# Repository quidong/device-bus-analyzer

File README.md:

# device-bus-analyzer

Collect, store, decode and inspect the internal bus telegrams of household appliances without ever transmitting on the bus.
Protocols: **BSH D-Bus** (Bosch / Siemens / Neff dishwashers) and the **Electrolux/AEG MACS bus** (heat-pump dryers; findings with confirmed/assumed/unknown status, see `docs/protocols/macs.md`; run detection names the run by the programme chosen before the start).

```
ESP32 board on the appliance bus ──ESPHome native API──▶ collector ─▶ SQLite (raw bursts, append-only)
                                                                         │
                                          decoder library + protocol spec (confirmed / assumed / unknown)
                                                                         │
                                    read-only HTTP API ─▶ web frontend (login) ─▶ MCP server (Claude Desktop)
```

* **Passive by design.** The collector only connects and subscribes to the device log; there is no code path that
  sends anything to a device or to the bus. The HTTP API is GET-only (a test asserts this). The web UI manages the local
  device list (add, edit, pause, delete with all its data) and never writes to an appliance.
* **Raw first.** Every burst is stored unchanged; decoded frames can be rebuilt at any time (`dba rebuild`), so better
  decoders never require re-recording.
* **Findings are data.** `src/device_bus_analyzer/spec/<protocol>.yaml` drives both the decoder and the findings page. Each
  command and field carries a status (`confirmed`, `assumed`, `unknown`) and its evidence.
* **No private data in the repository.** Logs stay on your server. `dba sanitize` strips SSID, MAC, IP, hostnames and keys
  before you share a log; a test scans the repository for such leftovers.

Hardware: the MACS board (schematic, KiCad, Gerber, enclosure) is in [`hardware/`](hardware/README.md).

## Quick start (Portainer / Docker)

1. Flash an ESPHome board with firmware that emits Logformat 1 (`docs/LOGFORMAT.md`). The matching ESPHome YAML for each device is shown in the app under **Devices > Firmware** (copy or download); the files live in `src/device_bus_analyzer/firmware/`: `bshdbus-analysis.example.yaml` for the dishwasher, `macs-analysis.example.yaml` + `macs_recorder.h` for the dryer.
   Enable the API encryption key in ESPHome.
2. In Portainer create a stack (Web editor: paste `docker-compose.yml`; the image `ghcr.io/quidong/device-bus-analyzer:latest` is built by GitHub Actions on every push to `main`) and set these **stack variables** (nothing secret is stored in the repo). Devices are *not* stack variables any more, add them in the UI (step 3):

| Variable | Meaning |
|---|---|
| `DBA_DEVICES` | *optional, one-time import*: `name@host[:port]/protocol`, comma separated, for example `geschirrspueler@192.0.2.10:6053/bshdbus` |
| `DBA_KEY_<NAME>` | *optional, one-time import*: ESPHome API encryption key of that device (`DBA_KEY_GESCHIRRSPUELER`) |
| `ADMIN_EMAIL` | the single admin account (login = e-mail address) |
| `ADMIN_PASSWORD_HASH` | argon2id hash, create with `echo -n 'your password' \| docker run -i --rm ghcr.io/quidong/device-bus-analyzer:latest dba hash-password` |
| `ADMIN_PASSWORD` | alternative to the hash (plain text in the stack; the hash is preferred) |
| `SESSION_SECRET` | optional: created on the first start and kept in the data volume; a value set here wins and is adopted (32+ random characters) |
| `API_TOKEN` | optional: created on the first start (shown on the *AI connection* page); a value set here wins and is adopted |
| `DBA_TZ` | display timezone, default `Europe/Berlin` |

3. Open `http://<host>:8080` (optional HTTPS: set `DBA_TLS=1` and `DBA_TLS_HOSTS`, then install the local CA once from `/tls/ca.crt`), sign in, then **Devices > New device**: choose type (dishwasher, washing machine, tumble dryer or your own), manufacturer, bus system and model (type, manufacturer and model
   are required). Every manufacturer and every bus is offered for every type; the manufacturer presets its usual bus, which you can
   change. Known models come from `src/device_bus_analyzer/catalog.yaml`; a model or manufacturer you type in is remembered and
   suggested again, even after its device is deleted. Then enter host, port and the
   ESPHome API key. Collection starts immediately and changes apply without a restart. Expose it in your LAN only; there is no password reset and no e-mail sending.
   If you must put it behind a reverse proxy, set `COOKIE_SECURE=1` and terminate TLS there.

**Device management.** Devices live in the SQLite database in the data volume (table `devices`, host and key included, so back up the
volume like a secret). The key is write-only: the UI shows only whether one is set. *Edit* changes type/model/connection, *Pause* stops collecting and keeps all data,
and *Delete* removes the device with all its frames, bursts, heartbeats, sessions and logs after you type its name (irreversible).
After saving a new device the **Firmware** page shows the recommended ESPHome YAML (and header) for its protocol with copy/download buttons. A device's name and protocol are fixed once
created, because the name identifies the data and the decoder depends on the protocol. **Upgrading an existing installation:**
leave `DBA_DEVICES` / `DBA_KEY_*` in the stack for the first start; they are imported once into the database without overwriting
anything configured in the UI. Afterwards open **Devices**, assign type/manufacturer/model, and remove the variables if you like.
Type, manufacturer and model are only recorded for now (they will let findings be split into "general for the protocol" and "specific
to a model"); decoding is unchanged. New catalogue entries are welcome as pull requests to `catalog.yaml`.

Devices that are only online sometimes (a dryer that connects when switched on) are fine: the collector reconnects forever
with back-off and the data model records board restarts and gaps explicitly.

## Analysis with Claude (MCP)
The app records and decodes what the spec already knows; the analysis of the unknown parts is done by **Claude** through the AI
connection (MCP). Record **complete runs** (choose a program, start it, let it finish) and note down what you did at the appliance and
when ("20:14 door opened"). Repeat interesting actions a few times. Then connect Claude (account menu → *AI connection*) and use one
of the example prompts on that page (overview, analyse a run with your actions, find display values, explain unknown commands,
write a contribution file, export a complete run). The device card shows how much of a recording is already **analysed**: the share
of telegram types (destination + command) that the spec describes (confirmed or assumed) or for which a finding was accepted. It
counts types, not telegrams, so a heartbeat sent every minute weighs no more than a command that appears twice.

There are two ways to give knowledge back to the project: **complete runs** (let Claude export a run with times relative to its
start and without host names, addresses or keys, and attach it to an issue) or **analysed findings** (let Claude write a contribution
file for `contributions/`; see *Contributing findings*).

The former companion (guided checks and manual marking) has been removed. Actions and findings recorded with it stay in the
database: devices that have them still show the **Learned** page (accept findings, export, spec suggestion), and the MCP tools
`list_markers` and `learn_analysis` still return them.

### Display values, Home Assistant, sharing
Accepted findings and values are shown next to the telegrams in the timeline and frames, and as **Now** on the device card.

**Home Assistant** (device card or Learned page): the page shows the current values and a ready `rest:` configuration that reads
`/api/{device}/state` with your API token. Decoding happens on the server; the ESPHome firmware only streams raw telegrams.

**Share** a contribution file written by Claude, or from the Learned page *Export findings* (JSON) or *Spec suggestion* (YAML for the protocol spec, always status *assumed*). Put the JSON
under `contributions/<protocol>/`; CI checks the file (`dba validate-contribution`, no telegrams, times, addresses or keys allowed).
`dba suggest-spec FILE` prints the YAML for a contribution.

**Backup** (header): download a consistent snapshot of the database, or restore one (type RESTORE; the file contains the ESPHome
keys, keep it private). **Help** explains the way from recording to finding. The MCP extension also offers `list_markers`, `learn_analysis`
and `device_state`.

The web interface is available in German, English, Spanish, French and Italian (switcher in the header; the browser language is detected, the choice is remembered).

### Device knowledge updates (no new image needed)
Protocol specs, the device catalogue and the recommended firmware live in the repository and can be refreshed in a running container:
**Device knowledge** (link on the start page) checks once a day (switchable) or on demand, and the MCP tool `update_knowledge` does the
same. Only data files listed in `knowledge-manifest.json` are fetched from GitHub, verified by SHA-256, validated with the normal spec and
catalogue checks and only then activated; a failed update changes nothing, *Reset* returns to the shipped files. Recorded data is never
touched and decoding uses the new knowledge at once. Checks are rate limited to one per minute. After changing a spec, the catalogue or a
firmware file run `dba build-knowledge` (a test fails otherwise). `DBA_KNOWLEDGE_URL` overrides the manifest address. The container needs
outbound HTTPS to raw.githubusercontent.com. The MCP tool `get_firmware` returns the firmware files of a device.

Security notes and what is protected how: see [SECURITY.md](SECURITY.md).

## Command line

```
dba import --source <name> --protocol bshdbus log1.txt log2.txt   # import saved ESPHome logs (date from file name or --date)
dba rebuild                                                       # re-decode frames from stored raw bursts
dba validate-spec bshdbus                                         # consistency check of the protocol spec
dba gaps log.txt                                                  # find lost bursts in a log
dba sanitize log.txt > clean.txt                                  # remove private details before sharing
dba collect | dba serve [--no-collector]
```

## MCP for Claude Desktop (extension)

The connection is meant for local operation and works with Claude only (Claude Desktop, Claude Code); the **AI connection** page in the app has the download, address and token. `extension/` is a Claude Desktop extension (`.mcpb`, Node). Build it with `cd extension && npm ci --omit=dev && npx @anthropic-ai/mcpb pack`
(the `extension` workflow also builds it on every change) and open the file in Claude Desktop. The install dialog asks for the
**analyzer URL** (for example `http://192.0.2.10:8089`, or `https://…` with `DBA_TLS=1` and the CA file from the HTTPS page) and the **API token** (`API_TOKEN` of the stack, stored as a sensitive value).
Nine tools (read access only): `list_sources`, `get_findings`, `list_runs`, `command_overview`, `command_values`, `timeline`, `frames`,
`raw_bursts`, `data_quality`. Every one is a GET against the API.

## Sender, ACK node and runs
A BSH D-Bus frame carries only its **destination**. Sender, receiver and the node that acknowledged (high nibble of the ACK
byte) are therefore *derived* from the spec (`nodes`, `acks`) and always shown with a status (`confirmed` / `assumed` /
`unknown`; unknown means the value is `null`). Per-field decode values carry their own status as well.

Telegrams are grouped into **runs** (program cycles): a run starts at the start command and ends at the last telegram before a
silent gap (rules in `spec/<protocol>.yaml`, `runs:`). Open a run in the frontend under "Runs", or pass its id as `run` to the API
(`/api/<source>/frames?run=<id>`, also `timeline` and `bursts`) and to the MCP tools.

## Development

```
pip install -e ".[dev]"
(cd extension && npm ci)   # optional: enables the extension test
pytest -q
```
Tests use synthetic telegrams only. Add real-device evidence to the spec as `evidence` text, never as log files.

## Contributing findings
Attach a contribution file written by Claude (or the JSON from **Export findings** on the Learned page) or an exported complete run to an issue, or open a pull request that changes `spec/<protocol>.yaml` (status + evidence) and, if useful, adds a synthetic test.
Please do not commit logs, MAC/IP addresses, SSIDs or serial numbers.

## Licenses
Code: MIT (`LICENSE`). Protocol documentation and spec files: CC BY 4.0 (`LICENSE-DOCS.md`).

## Design principles of the UI

- **Everything that can change is live.** Regions marked `data-live="…"` are refreshed from the server every few seconds (paused while the tab is hidden or a field in the region has focus); a changed list of devices reloads the page. New pages must mark their changing parts the same way (`static/ui.js`).
- **Settings page** (account menu → Settings): time zone, sign-in duration, knowledge update address, HTTPS (restart needed), renew the API token, change the password. Values saved there win over the stack variables, which only provide the defaults.
- **One account menu** (avatar, top right) holds language (a select), help, AI connection, knowledge, HTTPS, backup and logout.
- **Device cards:** icon and name open the device (its runs); all actions are uniform icon buttons with a tooltip (telegrams, Home Assistant, firmware, pause/resume, edit = pencil, delete = bin); the card shows the analysed share instead of the telegram count.

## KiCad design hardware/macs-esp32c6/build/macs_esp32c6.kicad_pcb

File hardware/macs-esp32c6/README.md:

# MACS-ESP32-C6 – universeller Adapter für Electrolux/AEG/Zanussi

ESPHome-Platine für den internen **MACS-Bus** von Electrolux-Geräten
(Waschmaschine, Trockner, Backofen, Kochfeld). Ein ESP32-C6 liest den Bus mit
und kann auch senden. Version 1.1 orientiert sich im Aufbau am
[BSH-Board von Bouni](https://github.com/Bouni/BSH-Board) (gleicher Zweck,
anderes Protokoll).

Grundlage: Reverse Engineering von
[agocsdaniel/esphome_electrolux_macs](https://github.com/agocsdaniel/esphome_electrolux_macs)
(Pinout, Pegel, Framing) und das Electrolux-Servicehandbuch *SidekickPC*.

---

## ⚠️ Sicherheit zuerst

* Die Elektronik in diesen Geräten ist **oft nicht vom Netz getrennt**. GND des
  MACS-Busses kann Netzpotenzial führen. Messungen nur mit isolierten
  Messgeräten, Gerät beim Anschließen vom Netz trennen (Stecker ziehen).
* **USB-C niemals benutzen, während die Platine am Gerät hängt.** USB ist nur
  zum ersten Flashen auf dem Tisch gedacht; danach Updates per WLAN (OTA).
* Der Sender ist fest mit dem Bus verbunden. Ein Basis-Pulldown hält ihn beim
  Booten aus; solange die Firmware nichts sendet, ist er hochohmig.

---

## Technische Daten

| | |
|---|---|
| Größe | 30 × 54 mm, 2 Lagen, 1,6 mm (Antenne ragt oben 6 mm über) |
| MCU | ESP32-C6-WROOM-1-N8 (WLAN 6, Thread/Zigbee, BLE) – WROOM statt MINI, weil JLCPCB das MINI nur in der teuren Standard-Bestückung verarbeitet |
| Versorgung | +12 V vom Bus (Standard) oder +5 V vom Bus (JP2), USB-C zum Flashen |
| Regler | AP63203 Step-Down, 3,8–32 V Eingang, feste 3,3 V |
| Schutz | TVS SMF15A auf +12 V, Z-Dioden 5,6 V auf DATA und +5 V, ESD-Schutz USB |
| MACS-Anschluss | RAST-2.5-Steckkante 4-polig direkt auf der Platine (1 = +12 V, 2 = +5 V, 3 = DATA, 4 = GND), Kontakte beidseitig, Codierschlitz zwischen 3 und 4 |
| Bus RX | Teiler 4k7/10k + 1 nF → GPIO18, 5 V → 3,4 V, Last < 0,4 mA |
| Bus TX | NPN + P-MOSFET schaltet +5 V über 100 Ω auf DATA ← GPIO19 |
| LEDs | Power (rot, fest), Status (grün, GPIO8), Bus-Aktivität (blau, GPIO21) |
| Extras | 12-V-Erkennung (GPIO0, ADC), Testpunkte DATA/GND/5V/3V3 und IO2/IO3/IO22, Pads für BOOT/RESET-Taster (nicht bestückt, Flashen geht über USB) |

### Lötbrücke

| | Auslieferung | Bedeutung |
|---|---|---|
| **JP2** | 1–2 gebrückt | 1–2 = Versorgung aus +12 V, 2–3 = aus +5 V (Leiterbahn zwischen 1–2 durchtrennen, 2–3 verzinnen) |

### Busstufe – Annahme zur Polarität
Laut den Messungen im Referenzprojekt ist DATA **in Ruhe 0 V** und aktiv
**5 V** (invertierter UART). Die Senderstufe ist deshalb ein High-Side-Treiber
(zieht DATA auf 5 V, Ruhe hochohmig). Beim ersten Anschluss zuerst nur
mitlesen (`macs-sniffer.yaml`) und an TP1 (DATA) gegen TP2 (GND) prüfen:
in Ruhe ≈ 0 V mit kurzen Ausschlägen. Liegt dort dauerhaft ~5 V an, ist die
Logik bei deinem Gerät umgekehrt – dann nicht senden und melden.

---

## Bestellung bei JLCPCB

1. **Gerber hochladen:** `fab/macs_esp32c6_gerber.zip`
   – 2 Lagen, 1,6 mm, Standardwerte; Farbe nach Wunsch.
   Die Antenne des ESP-Moduls ragt absichtlich 6 mm über den Platinenrand
   (beste Funkleistung). Fragt JLC bei der Bestückung nach, das bestätigen.
2. **PCB Assembly** aktivieren, „Assemble top side“.
3. **BOM** `fab/macs_esp32c6_bom.csv` und **CPL** `fab/macs_esp32c6_cpl.csv`
   hochladen. Alle Bauteile haben LCSC-Nummern.
4. In der **Bauteil-Vorschau die Drehung prüfen** (v. a. Dioden, USB-C,
   SOT-23-Teile). Das ist bei JLC immer nötig – Abweichungen dort per
   Drehknopf korrigieren.
5. **PCBA Type „Economic“**, Oberfläche **LeadFree HASL** (die Steckerfedern
   sind verzinnt, Zinn auf Zinn kontaktiert gut; ENIG wäre ~15 $ teurer),
   Dicke **1,6 mm** (RAST-Norm 1,5 ± 0,14; 1,6 funktioniert beim BSH-Board).
   Die CPL enthält bereits die JLC-Drehkorrekturen (SOT-23 +180°,
   SOT-23-6/TSOT-23-6 +270°, in der JLC-Vorschau geprüft).
6. J2 (Steckkante), die Taster SW1/SW2 und die Testpunkte sind nicht bestückt
   und stehen deshalb nicht in BOM/CPL.

### Steckkante und Kabel
Vorbild ist die Steckkante des [BSH-Boards](https://github.com/Bouni/BSH-Board),
auf 4 Pole erweitert:

* Zunge mit 4 Kontaktflächen im 2,5-mm-Raster, **oben und unten** (über
  Durchkontaktierungen verbunden) – egal, auf welcher Seite die Federn des
  Steckers liegen. Keine Lötpaste auf den Kontakten.
* Aussparung 13,2 × 2,5 mm: Die Platinenwangen links und rechts führen den
  Stecker seitlich.
* Codierschlitz 1,0 mm (JLCPCB-Minimum) zwischen Kontakt 3 und 4 – passt zum
  Trockner. Stecker **mit** Codiersteg (Lumberg 3517 04 K01) gehen nur richtig
  herum drauf, Stecker **ohne** Codierung (Würth WR-RAST 667101210104) passen
  ebenfalls.

**Kabel:** an beiden Enden derselbe Schneidklemm-Stecker, Adern 1:1
(1→1 … 4→4). Leitung LiYY 4 × 0,25 mm² (passt für Lumberg 0,14–0,38 mm² und
Würth AWG 24–22).

* Stecker gleichmäßig eindrücken (Schraubstock, Adern sauber abgeschnitten),
  danach Durchgang messen und dabei am Kabel wackeln.
* **Ohne Codierung kann man den Stecker umgedreht aufstecken** (1↔4, 2↔3 –
  dann liegen 12 V auf GND). Kontakt 1 am Stecker und an beiden Platinen
  farbig markieren und vor dem Einschalten prüfen: zwischen Pad 1 und 4 an
  unserer Platine müssen bei eingestecktem Kabel +12 V anliegen.

---

## Inbetriebnahme

1. Platine **ohne Gerät** per USB-C an den PC. Der ESP32-C6 wird über seine
   eingebaute USB-Schnittstelle ohne Taster geflasht (ESPHome/esptool setzen
   ihn selbst in den Download-Modus).
2. `firmware/macs-sniffer.yaml` (nur mitlesen; für den Trockner empfiehlt sich die Firmware aus `src/device_bus_analyzer/firmware/macs-analysis.example.yaml`) oder
   `firmware/macs-washer.yaml` mit ESPHome flashen (`secrets.yaml` mit
   `wifi_ssid`/`wifi_password` anlegen; `__API_KEY__`/`__AP_PASSWORD__`
   ersetzt der Device Builder beim Anlegen). Danach USB abziehen.
   **Fabrikneues Modul ohne Firmware:** Der Chip startet ohne gültiges
   Programm ständig neu, Windows meldet das USB-Gerät dann alle paar
   Sekunden neu an. Kommt das Flashen nicht durch: die Pads von SW1 (BOOT)
   beim Einstecken mit einer Pinzette überbrücken – der Chip bleibt dann im
   Download-Modus.
3. Gerät stromlos machen, Platine anschließen, Gerät einschalten.
   Im ESPHome-Log erscheinen die Frames als Hex; „Bus 12V“ zeigt ~12 V.
4. Mitschnitt auswerten: `python3 tools/macs_frames.py < log.txt`
5. Waschmaschine mit EWX-Steuerung: `firmware/macs-washer.yaml` (Decoder von
   agocsdaniel). Trockner: dessen EDR-Beispiel übernehmen.

---

## Dateien

| Pfad | Inhalt |
|---|---|
| `circuit.py` | Schaltung als Code (SKiDL) – **Quelle der Wahrheit** |
| `build/macs_esp32c6.kicad_pro` | KiCad-Projekt (öffnet in KiCad 7, 8, 9): Schaltplan (hierarchisch, Netzlabel-Stil) + Leiterplatte, Regeln für JLCPCB hinterlegt |
| `fab/` | Gerber-ZIP, BOM, CPL, Schaltplan- und Layout-PDF |
| `firmware/` | ESPHome-Konfigurationen |
| `tools/macs_frames.py` | MACS-Frames aus Logs zerlegen, Prüfsumme prüfen |
| `tests/test_board.py` | Testsuite (Schaltung, Layout/DRC, Fertigungsdaten, Firmware) |
| `make_all.sh` | Kompletter Neuaufbau inkl. Autorouting (Freerouting) und Tests |
| `build_pcb.py --use-ses` | Platine mit dem gespeicherten, geprüften Routing neu erzeugen (ohne neues Autorouting) |

Der Schaltplan ist automatisch aus `circuit.py` erzeugt: Verbindungen laufen
über Netzlabels statt Drähte. Für Änderungen am besten `circuit.py` anpassen
und `make_all.sh` laufen lassen; kleine Layout-Korrekturen gehen direkt in
KiCad.

## Tests

```
python3 -m pytest -q tests/
```

Geprüft wird u. a.: Pinout der MACS-Stecker, GPIO-Zuordnung, sichere
Strapping-Pins, Pegel des RX-Teilers, Reglerausgang 3,30 V, ADC-Bereich,
jedes Pad auf der Platine gegen die Netzliste, DRC ohne Fehler und ohne offene
Verbindungen, BOM/CPL konsistent mit LCSC-Nummern, ESPHome-YAML passt zur
Platine, MACS-Prüfsumme und Log-Parser.

---

## Gehäuse (3D-Druck)

`enclosure/macs_gehaeuse_unterteil.stl` und `enclosure/macs_gehaeuse_deckel.stl`
(Deckel liegt schon in Druckausrichtung, Oberseite aufs Bett; er ist um die X-Achse gedreht, nicht gespiegelt – zum Montieren wieder um die X-Achse umdrehen, dann sitzt die USB-Aussparung an der USB-Seite).

* Platine ohne Befestigungslöcher: liegt auf einem umlaufenden Steg, der Deckel
  drückt sie mit Rippen fest. Deckel hält per Steckrand + Rastnasen.
* **Stecker:** Führungswände links/rechts vor der Zunge (0,3 mm Spiel, kein
  seitliches Verrutschen), zwei Niederhalter im Deckel über den Steckerenden
  (kein Abheben, Mitte frei für die Adern). Die Führungswände sind zugleich
  Anschlag für die Platine.
* **Kabel:** verlässt das Gehäuse stirnseitig durch eine geteilte Durchführung,
  die das Kabel (Ø 5 mm) leicht klemmt – das ist die Zugentlastung, der Stecker
  kann nicht abgezogen werden.
* **Abgedichtet:** keine Öffnungen für USB/Taster (USB nur zum ersten Flashen,
  Platine dafür herausnehmen); der Deckel greift mit einem 3 mm hohen Steckrand
  in das Unterteil (Labyrinth), die LEDs leuchten durch 1,2 mm Restwand.
  Für noch mehr Dichtheit vor dem Schließen eine dünne Silikonraupe auf die
  Oberkante des Unterteils.
* **Wandstärken für den FDM-Druck:** alle tragenden Wände 2,0 mm (Boden und
  Deckel 2,4 mm wegen der 0,4 mm tiefen Gravur), einzige Ausnahme sind die
  1,2-mm-Fenster über den LEDs (JLC3DP-Minimum). Geprüft mit
  `python3 enclosure/wall_thickness.py` und im Test.
* **Magnete wie beim BSH-Board:** 4 × Neodym 5 × 5 mm (z. B. supermagnete
  S-05-05-N) in Laschen außen an den Längsseiten. Die Bohrung geht durch,
  der Magnet sitzt bündig mit der Unterseite und liegt direkt am Blech. Mit
  einem Tropfen Sekundenkleber sichern, Polung bei allen gleich.
* **LEDs:** drei Lichtleiter im Deckel (PWR, ST, ACT) mit 1,2 mm Restwand –
  bei weißem ASA leuchten sie durch.
* Druck: ASA weiß (wärmefest bis ~98 °C, im Trockner wird es warm), 0,2 mm
  Schicht, ohne Stützmaterial. Bei JLC3DP: FDM, ASA, White.
* Steckermaße sind Annahmen (Breite 12,5, Höhe ≤ 4,8 mm über der Platine):
  Passt dein Stecker nicht, `plug_*` in `enclosure/make_enclosure.py` anpassen
  und `python3 enclosure/make_enclosure.py` laufen lassen.

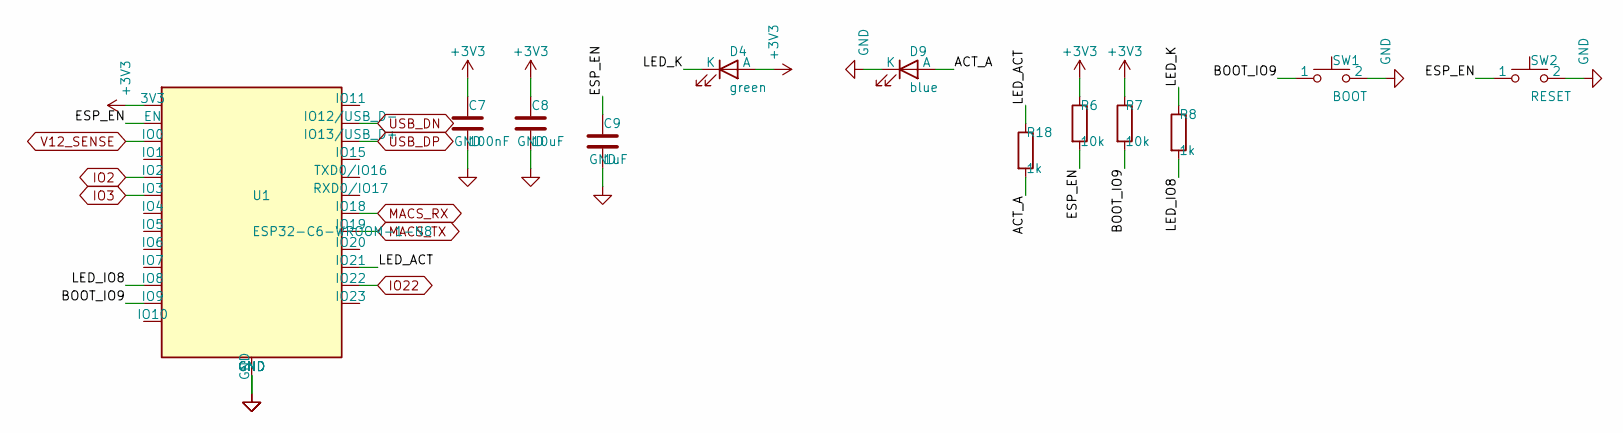
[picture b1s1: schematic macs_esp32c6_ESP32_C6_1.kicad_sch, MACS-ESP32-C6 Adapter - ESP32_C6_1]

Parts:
C7: 100nF; C_0402_1005Metric; LCSC C307331
C8: 10uF; C_0603_1608Metric; LCSC C96446
C9: 1uF; C_0402_1005Metric; LCSC C52923
D4: green; LED_0603_1608Metric; MPN green; LCSC C12624
D9: blue; LED_0603_1608Metric; MPN blue; LCSC C965807
R6, R7: 10k; R_0402_1005Metric; LCSC C25744
R8, R18: 1k; R_0402_1005Metric; LCSC C11702
SW1: BOOT; SW_TS-3025; MPN TS-3025-B-C-B; LCSC C2689695
SW2: RESET; SW_TS-3025; MPN TS-3025-B-C-B; LCSC C2689695
U1: ESP32-C6-WROOM-1-N8; ESP32-C6-WROOM-1; MPN ESP32-C6-WROOM-1-N8; LCSC C5366877

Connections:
+3V3: C7.1, C8.1, D4.2 (A), R6.1, R7.1, U1.2 (3V3); also elsewhere on the board
ACT_A: D9.2 (A), R18.2
BOOT_IO9: R7.2, SW1.1, U1.15 (IO9)
ESP_EN: C9.1, R6.2, SW2.1, U1.3 (EN)
GND: C7.2, C8.2, C9.2, D9.1 (K), SW1.2, SW2.2, U1.1 (GND), U1.28 (GND), U1.29 (GND); also elsewhere on the board
IO2: U1.27 (IO2); also elsewhere on the board
IO3: U1.26 (IO3); also elsewhere on the board
IO22: U1.20 (IO22); also elsewhere on the board
LED_ACT: R18.1, U1.19 (IO21)
LED_IO8: R8.2, U1.10 (IO8)
LED_K: D4.1 (K), R8.1
MACS_RX: U1.16 (IO18); also elsewhere on the board
MACS_TX: U1.17 (IO19); also elsewhere on the board
USB_DN: U1.13 (IO12/USB_D-); also elsewhere on the board
USB_DP: U1.14 (IO13/USB_D+); also elsewhere on the board
V12_SENSE: U1.8 (IO0); also elsewhere on the board

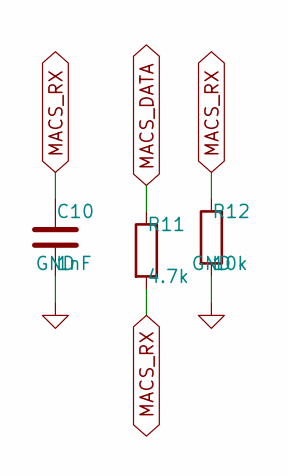
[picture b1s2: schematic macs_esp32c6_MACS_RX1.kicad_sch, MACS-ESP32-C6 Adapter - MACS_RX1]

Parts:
C10: 1nF; C_0402_1005Metric; LCSC C1523
R11: 4.7k; R_0402_1005Metric; LCSC C25900
R12: 10k; R_0402_1005Metric; LCSC C25744

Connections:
GND: C10.2, R12.2; also elsewhere on the board
MACS_DATA: R11.1; also elsewhere on the board
MACS_RX: C10.1, R11.2, R12.1; also elsewhere on the board

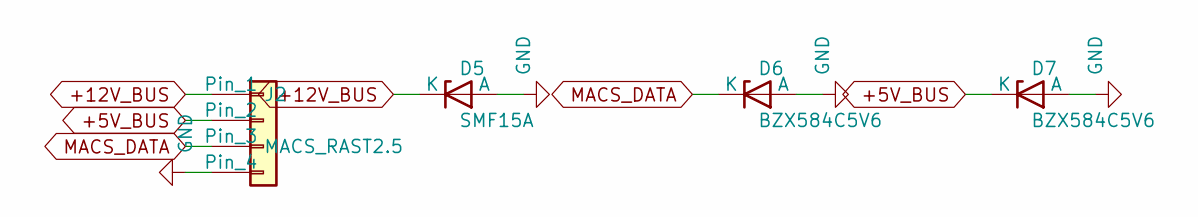
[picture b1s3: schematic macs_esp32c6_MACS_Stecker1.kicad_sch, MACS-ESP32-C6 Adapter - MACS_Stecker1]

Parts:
D5: SMF15A; D_SOD-123F; MPN SMF15A; LCSC C353311
D6, D7: BZX584C5V6; D_SOD-523; MPN BZX584C5V6; LCSC C19077464
J2: MACS_RAST2.5; RAST25_Direkt_1x04_K34

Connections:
+5V_BUS: D7.1 (K), J2.2; also elsewhere on the board
+12V_BUS: D5.1 (K), J2.1; also elsewhere on the board
GND: D5.2 (A), D6.2 (A), D7.2 (A), J2.4; also elsewhere on the board
MACS_DATA: D6.1 (K), J2.3; also elsewhere on the board

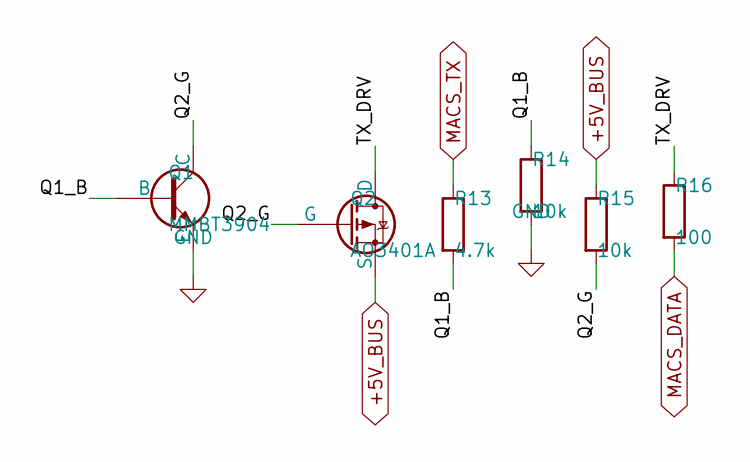
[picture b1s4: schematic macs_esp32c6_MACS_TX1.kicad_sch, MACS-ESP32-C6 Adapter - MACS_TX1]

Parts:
Q1: MMBT3904; SOT-23; MPN MMBT3904; LCSC C20526
Q2: AO3401A; SOT-23; MPN AO3401A; LCSC C15127
R13: 4.7k; R_0402_1005Metric; LCSC C25900
R14, R15: 10k; R_0402_1005Metric; LCSC C25744
R16: 100; R_0402_1005Metric; LCSC C25076

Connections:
+5V_BUS: Q2.2 (S), R15.1; also elsewhere on the board
GND: Q1.2 (E), R14.2; also elsewhere on the board
MACS_DATA: R16.2; also elsewhere on the board
MACS_TX: R13.1; also elsewhere on the board
Q1_B: Q1.1 (B), R13.2, R14.1
Q2_G: Q1.3 (C), Q2.1 (G), R15.2
TX_DRV: Q2.3 (D), R16.1

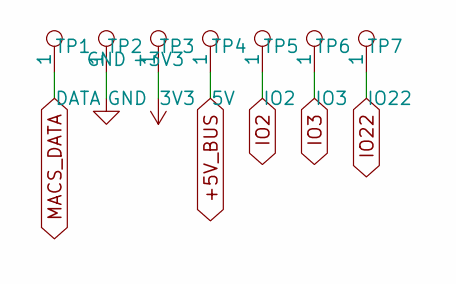
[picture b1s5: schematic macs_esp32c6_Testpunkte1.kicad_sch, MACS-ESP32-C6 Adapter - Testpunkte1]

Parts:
TP1: DATA; TestPoint_Pad_D1.0mm
TP2: GND; TestPoint_Pad_D1.0mm
TP3: 3V3; TestPoint_Pad_D1.0mm
TP4: 5V; TestPoint_Pad_D1.0mm
TP5: IO2; TestPoint_Pad_D1.0mm
TP6: IO3; TestPoint_Pad_D1.0mm
TP7: IO22; TestPoint_Pad_D1.0mm

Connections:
+3V3: TP3.1; also elsewhere on the board
+5V_BUS: TP4.1; also elsewhere on the board
GND: TP2.1; also elsewhere on the board
IO2: TP5.1; also elsewhere on the board
IO3: TP6.1; also elsewhere on the board
IO22: TP7.1; also elsewhere on the board
MACS_DATA: TP1.1; also elsewhere on the board

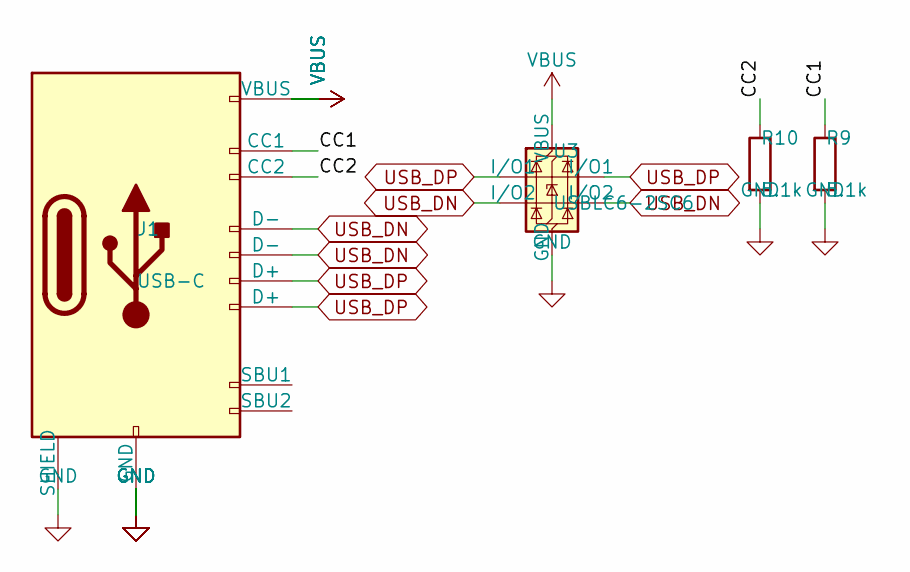
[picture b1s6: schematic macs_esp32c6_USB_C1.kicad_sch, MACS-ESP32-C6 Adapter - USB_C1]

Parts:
J1: USB-C; USB_C_Receptacle_HRO_TYPE-C-31-M-12; MPN TYPE-C-31-M-12; LCSC C165948
R9, R10: 5.1k; R_0402_1005Metric; LCSC C25905
U3: USBLC6-2SC6; SOT-23-6; MPN USBLC6-2SC6; LCSC C7519

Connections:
CC1: J1.A5 (CC1), R9.1
CC2: J1.B5 (CC2), R10.1
GND: J1.A1 (GND), J1.A12 (GND), J1.B1 (GND), J1.B12 (GND), J1.S1 (SHIELD), R9.2, R10.2, U3.2 (GND); also elsewhere on the board
USB_DN: J1.A7 (D-), J1.B7 (D-), U3.3 (I/O2), U3.4 (I/O2); also elsewhere on the board
USB_DP: J1.A6 (D+), J1.B6 (D+), U3.1 (I/O1), U3.6 (I/O1); also elsewhere on the board
VBUS: J1.A4 (VBUS), J1.A9 (VBUS), J1.B4 (VBUS), J1.B9 (VBUS), U3.5 (VBUS); also elsewhere on the board

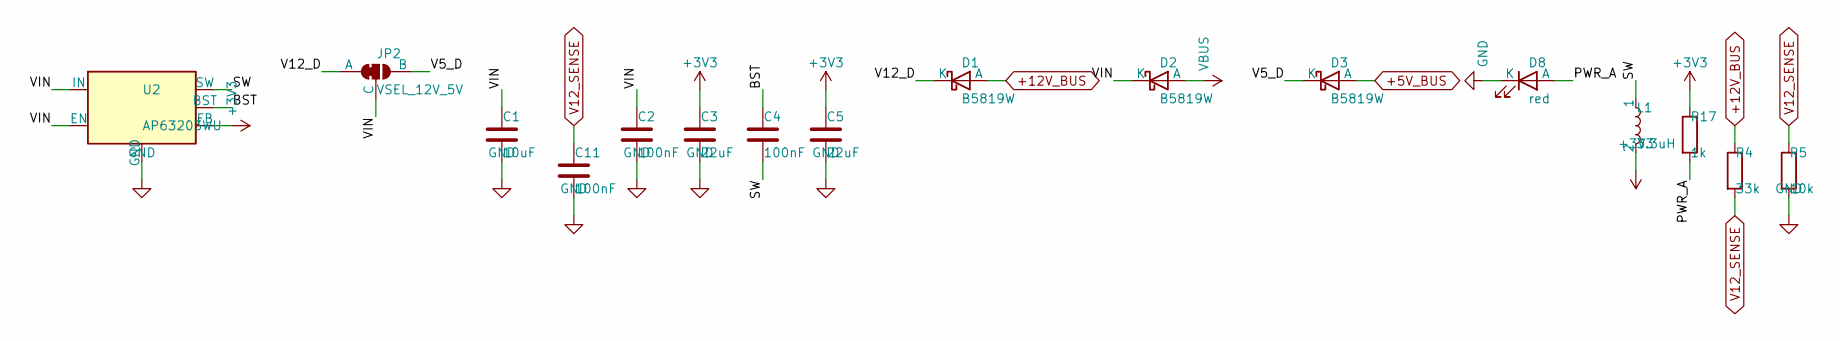
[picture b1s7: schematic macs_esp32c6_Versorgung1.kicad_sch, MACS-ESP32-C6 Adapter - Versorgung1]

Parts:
C1: 10uF; C_0603_1608Metric; LCSC C96446
C2, C4, C11: 100nF; C_0402_1005Metric; LCSC C307331
C3, C5: 22uF; C_0805_2012Metric; LCSC C45783
D1, D2, D3: B5819W; D_SOD-123; MPN B5819W; LCSC C8598
D8: red; LED_0603_1608Metric; MPN red; LCSC C2286
JP2: VSEL_12V_5V; SolderJumper-3_P1.3mm_Bridged12_RoundedPad1.0x1.5mm
L1: 3.3uH; L_1008_2520Metric; MPN 3.3uH 1008; LCSC C5832373
R4: 33k; R_0402_1005Metric; LCSC C25779
R5: 10k; R_0402_1005Metric; LCSC C25744
R17: 1k; R_0402_1005Metric; LCSC C11702
U2: AP63203WU; TSOT-23-6; MPN AP63203WU-7; LCSC C780769

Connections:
+3V3: C3.1, C5.1, L1.2, R17.1, U2.1 (FB); also elsewhere on the board
+5V_BUS: D3.2 (A); also elsewhere on the board
+12V_BUS: D1.2 (A), R4.1; also elsewhere on the board
BST: C4.1, U2.6 (BST)
GND: C1.2, C2.2, C3.2, C5.2, C11.2, D8.1 (K), R5.2, U2.4 (GND); also elsewhere on the board
PWR_A: D8.2 (A), R17.2
SW: C4.2, L1.1, U2.5 (SW)
V5_D: D3.1 (K), JP2.3 (B)
V12_D: D1.1 (K), JP2.1 (A)
V12_SENSE: C11.1, R4.2, R5.1; also elsewhere on the board
VBUS: D2.2 (A); also elsewhere on the board
VIN: C1.1, C2.1, D2.1 (K), JP2.2 (C), U2.2 (EN), U2.3 (IN)

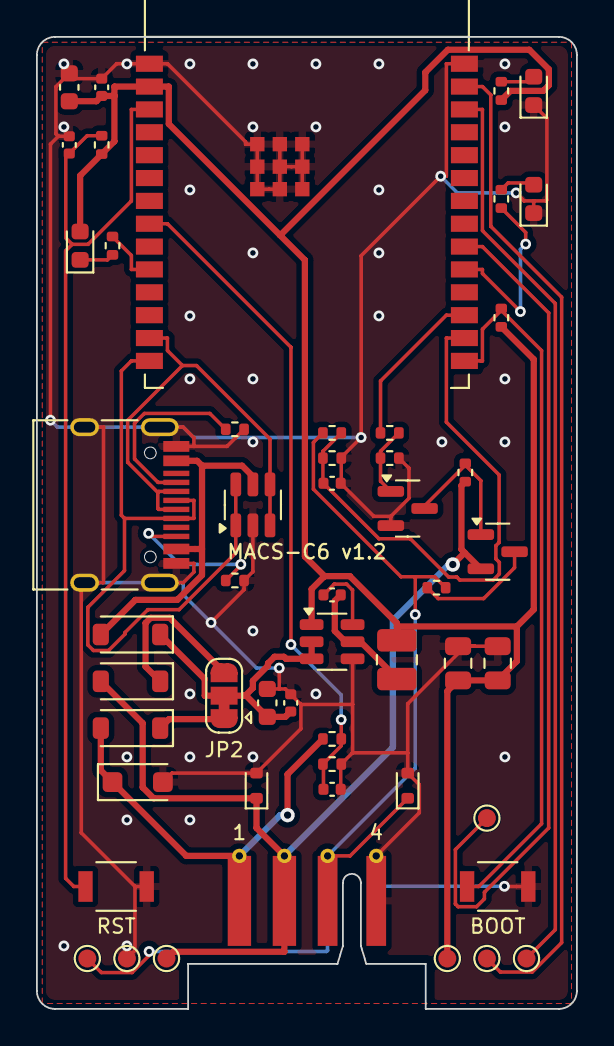
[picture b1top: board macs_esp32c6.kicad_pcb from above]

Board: 2 copper layers, 30.0 x 54.0 mm, 52 parts (0 on the bottom side), 31 nets.

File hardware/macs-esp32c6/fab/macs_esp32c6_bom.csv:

Comment,Designator,Footprint,LCSC Part #,Quantity
10uF,"C1,C8",C_0603_1608Metric,C96446,2
100nF,"C2,C4,C7,C11",C_0402_1005Metric,C307331,4
22uF,"C3,C5",C_0805_2012Metric,C45783,2
1uF,C9,C_0402_1005Metric,C52923,1
1nF,C10,C_0402_1005Metric,C1523,1
B5819W,"D1,D2,D3",D_SOD-123,C8598,3
green,D4,LED_0603_1608Metric,C12624,1
SMF15A,D5,D_SOD-123F,C353311,1
BZX584C5V6,"D6,D7",D_SOD-523,C19077464,2
red,D8,LED_0603_1608Metric,C2286,1
blue,D9,LED_0603_1608Metric,C965807,1
USB-C,J1,USB_C_Receptacle_HRO_TYPE-C-31-M-12,C165948,1
3.3uH,L1,L_1008_2520Metric,C5832373,1
MMBT3904,Q1,SOT-23,C20526,1
AO3401A,Q2,SOT-23,C15127,1
33k,R4,R_0402_1005Metric,C25779,1
10k,"R5,R6,R7,R12,R14,R15",R_0402_1005Metric,C25744,6
1k,"R8,R17,R18",R_0402_1005Metric,C11702,3
5.1k,"R9,R10",R_0402_1005Metric,C25905,2
4.7k,"R11,R13",R_0402_1005Metric,C25900,2
100,R16,R_0402_1005Metric,C25076,1
ESP32-C6-WROOM-1-N8,U1,ESP32-C6-WROOM-1,C5366877,1
AP63203WU,U2,TSOT-23-6,C780769,1
USBLC6-2SC6,U3,SOT-23-6,C7519,1
